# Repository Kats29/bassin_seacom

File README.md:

# Bassin Laboratoire SEACom - ISEN

Ce projet vise à remettre le bassin de test du laboratoire SEACom de l'ISEN au goût du jour. Pour cela, une interface Web est déployée sur un serveur Ethernet hébergé sur une carte Beaglebone Black qui communique avec le bassin via un shield customisé.

## TODO

### Partie Logicielle

- écrire une suite de tests exhaustive qui permet de comprendre ce qui doit être envoyé par le backend en fonction des commandes exécutées
- définir les trames de messages dans la documentation
- compléter la description de cette documentation (à partir de "Redémarrage des commandes numériques (RESET)")

### Partie Matérielle

- Imprimer ou découper à la CNC le couvercle du boitier de la carte
- Ajouter la vitre plexi devant les LED
- Produire la nouvelle version de la carte électronique
- acheter les différents composant manquant pour autonomiser le boitier
	- [prise filtre 230V](https://fr.rs-online.com/web/p/filtres-iec/1676800?searchId=2fb21e5c-5856-4a20-a56e-df45db2b0a76) (ça sera serré mais normalement ça passe)
    - [Alim 5V](https://fr.rs-online.com/web/p/alimentations-a-decoupage/0413673?searchId=7ffa1f5d-4cfa-4edf-9e52-69dc6d7725a8)
    - connecteur DB9 de facade

## Installation

### Configuration de la carte Beaglebone

Premièrement, afin d'avoir accès à tous les ports GPIO de la carte, celle-ci doit être démarrée à partir d'une carte SD au lieu de sa mémoire interne. Pour ce faire, téléchargez [la dernière image de Debian pour Beaglenone Black](https://www.beagleboard.org/distros) et flashez-la sur votre carte SD. Faites attention de bien choisir une image et non pas un flasher eMMC (le nom devrait finir par `4GB microSD IoT`).

Puisque les dernières versions ont un serveur nginx préinstallé, c'est ce que ce projet va utiliser.

Afin de vous connecter au Beaglebone, connecter le câble ethernet à votre pc et configurer votre carte réseau pour avoir une IPv4 telle que 192.168.7.4, via la commande `sudo ifconfig enp3s0 192.168.7.4` (en remplaçant enp3s0 par le nom de votre interface réseau).

Une fois la carte SD insérée dans la Beaglebone et celle-ci branchée sur le même réseau que votre ordinateur, vous pourrez ouvrir une console `ssh` grâce à la commande suivante :

```sh
ssh debian@192.168.7.3
```

Le mot de passe par défaut est `temppwd`.

Afin de configurer nginx, ouvrez le fichier `/etc/nginx/sites-enabled/default` et remplacez la ligne `root /var/www` par `root /home/debian/dist`. Enregistrez le fichier.

Finalement, il faut ouvrir le port 3333 de la Beaglebone pour permettre la connection TCP entre l'interface et le backend :

```sh
sudo nft add table ip filter
sudo nft add chain ip filter INPUT { type filter hook input priority 0 \; }
sudo nft add rule ip filter INPUT tcp dport 3333 accept
sudo nft list ruleset # pour vérifier que les règles ont bien été appliquées
sudo nft list ruleset | sudo tee -a /etc/nftables.conf # pour les sauvegarder
```

Vous pouvez maintenant quitter la console `ssh` avec la commande :

```sh
exit
```

### Compilation du projet

La compilation nécessite d'avoir podman, podman-compose et git d'installés sur le pc.
Clonez et compilez le projet GitHub sur votre ordinateur avec les commandes suivantes :

```sh
git clone https://github.com/Kats29/bassin_seacom.git
cd bassin_seacom
podman build .
podman compose run --rm arm-builder
```

Une fois que le projet est bien compilé (penser à vérifier les logs pour cela) vous pouvez envoyer la release sur la Beaglebone via le script `./.send.sh`.

Tapez le mot de passe de la Beaglebone lorsqu'il vous est demandé.

Vous pouvez à présent rouvrir une console `ssh` pour démarrer le backend :

```sh
ssh debian@192.168.7.3
```

Tapez le mot de passe.

```sh
sudo systemctl restart backend.service
```

Si tout va bien, vous devez avoir quelque chose qui ressemble à ci-dessous en tapant la commande  `sudo systemctl status backend.service` :
```sh
● backend.service - Backend du bassin
     Loaded: loaded (/etc/systemd/system/backend.service; enabled; preset: enabled)
     Active: active (running) since Fri 2025-03-14 21:15:03 CET; 5s ago
   Main PID: 2041 (backend)
      Tasks: 1 (limit: 1024)
     Memory: 72.0K
        CPU: 61ms
     CGroup: /system.slice/backend.service
             └─2041 /home/debian/backend

Mar 14 21:15:03 bassin systemd[1]: Started backend.service - Backend du bassin.
Mar 14 21:15:03 bassin backend[2041]: Starting backend...
```

Si vous souhaitez éditer la configuration du service, elle se trouve ici `/etc/systemd/system/backend.service` et nécessite un redémarrage de systemctl via `sudo systemctl daemon-reload`.

### Accès à l'interface

Vous pouvez à présent vous connecter à l'interface depuis votre navigateur internet, en tapant `192.168.7.3:9090` dans la barre d'adresse.

## Branchement

### Installation de la Beaglebone

### Raccordement réseau

### Communication avec le bassin

## Documentation

Une fois le projet cloné, la documentation technique du code peut être générée grâce à la commande :

```sh
make doc
```

La documentation devrait s'ouvrir dans un navigateur. Sinon, elle peut être visualisée dans un navigateur en ouvrant les fichiers `index.html` générés dans `target/doc/common`, `target/armv7-unknown-linux-musleabihf/doc/backend` et `target/wasm32-unknown-unknown/doc/frontend`

## Utilisation

L'accès se fait via deux plateformes : [cockpit](https://192.168.7.3:9090/system) pour le monitoring et le [site web pour le contrôle des bras](http://192.168.7.3/).

### Apparence et organisation

L'interface est constituée d'une seule vue, qui est séparée en trois zones : une vue centrale, et deux panneaux latéraux. En cas de nécéssité, une fenêtre d'erreur peut également s'ouvrir devant la vue centrale.

#### Vue centrale

La vue centrale représente une visualisation de l'état actuel du bassin, ainsi que des commandes prévues.

Sa partie supérieure montre une vue du dessus en séparant les moitiés droite et gauche du bassin. La même séparation est visible sur la partie inférieure, qui elle montre une vue de côté du bassin (pour visualiser la profondeur).

Les cadres noirs délimitent les zones où chacun des deux bras peut se déplacer, et les symboles  en noir symbolisent la position actuelle de chaque bras. Les symboles  grisés montrent le prochain mouvement pouvant être ajouté.

#### Panneau gauche

Le panneau latéral gauche montre deux choses :

* Les coordonnées du prochain mouvement à ajouter pour chaque bras.

* L'état actuel du bassin, sous formes d'indicateurs colorés (rouges ou verts, gris si le bassin n'est pas connecté).
	* En face de chaque coordonnée, un indicateur passe au rouge si un mouvement est en cours sur cet axe.
	* Sous les coordonnées, d'autres informations sont données sous cette forme.

#### Panneau droit

Le panneau latéral droit montre simplement la liste des mouvement prévus pour chaque bras, dans l'ordre chronologique.

#### Fenêtre d'erreur

### Commandes d'alimentation

La première chose à faire pour allumer le bassin est de le mettre physiquement sous tension. Une fois que c'est fait, l'alimentation peut être contrôlée à distance par l'interface.

#### Allumer le bassin

Pour allumer le bassin, allez dans le menu `Alimentation` et cliquez sur `Démarrer`. Après un démarrage de cette façon, une commande de RESET (expliquée plus loin) et de remise à l'origine doivent obligatoirement être effectuées dans cet ordre.

Après appui, les indicateurs `Bassin alimenté` et `Bassin démarré` devraient être au vert.

#### Éteindre le bassin

Une fois le bassin sous tension et démarré, le menu `Alimentation` devrait contenir un bouton `Arrêter`, qui doit éteindre le bassin.

Après appui, l'indicateur `Bassin démarré` devrait repasser au rouge.

#### Redémarrage des commandes numériques (RESET)

### Gestion des mouvements

#### Ajouter un mouvement

#### Supprimer un mouvement

#### Modifier un mouvement

### Effectuer un mouvement

#### Commandes générales

#### Commandes par bras

#### Commandes par axe

### Sauvegarde et importation de positions

#### Sauvegarder la configuration

#### Importer une configuration

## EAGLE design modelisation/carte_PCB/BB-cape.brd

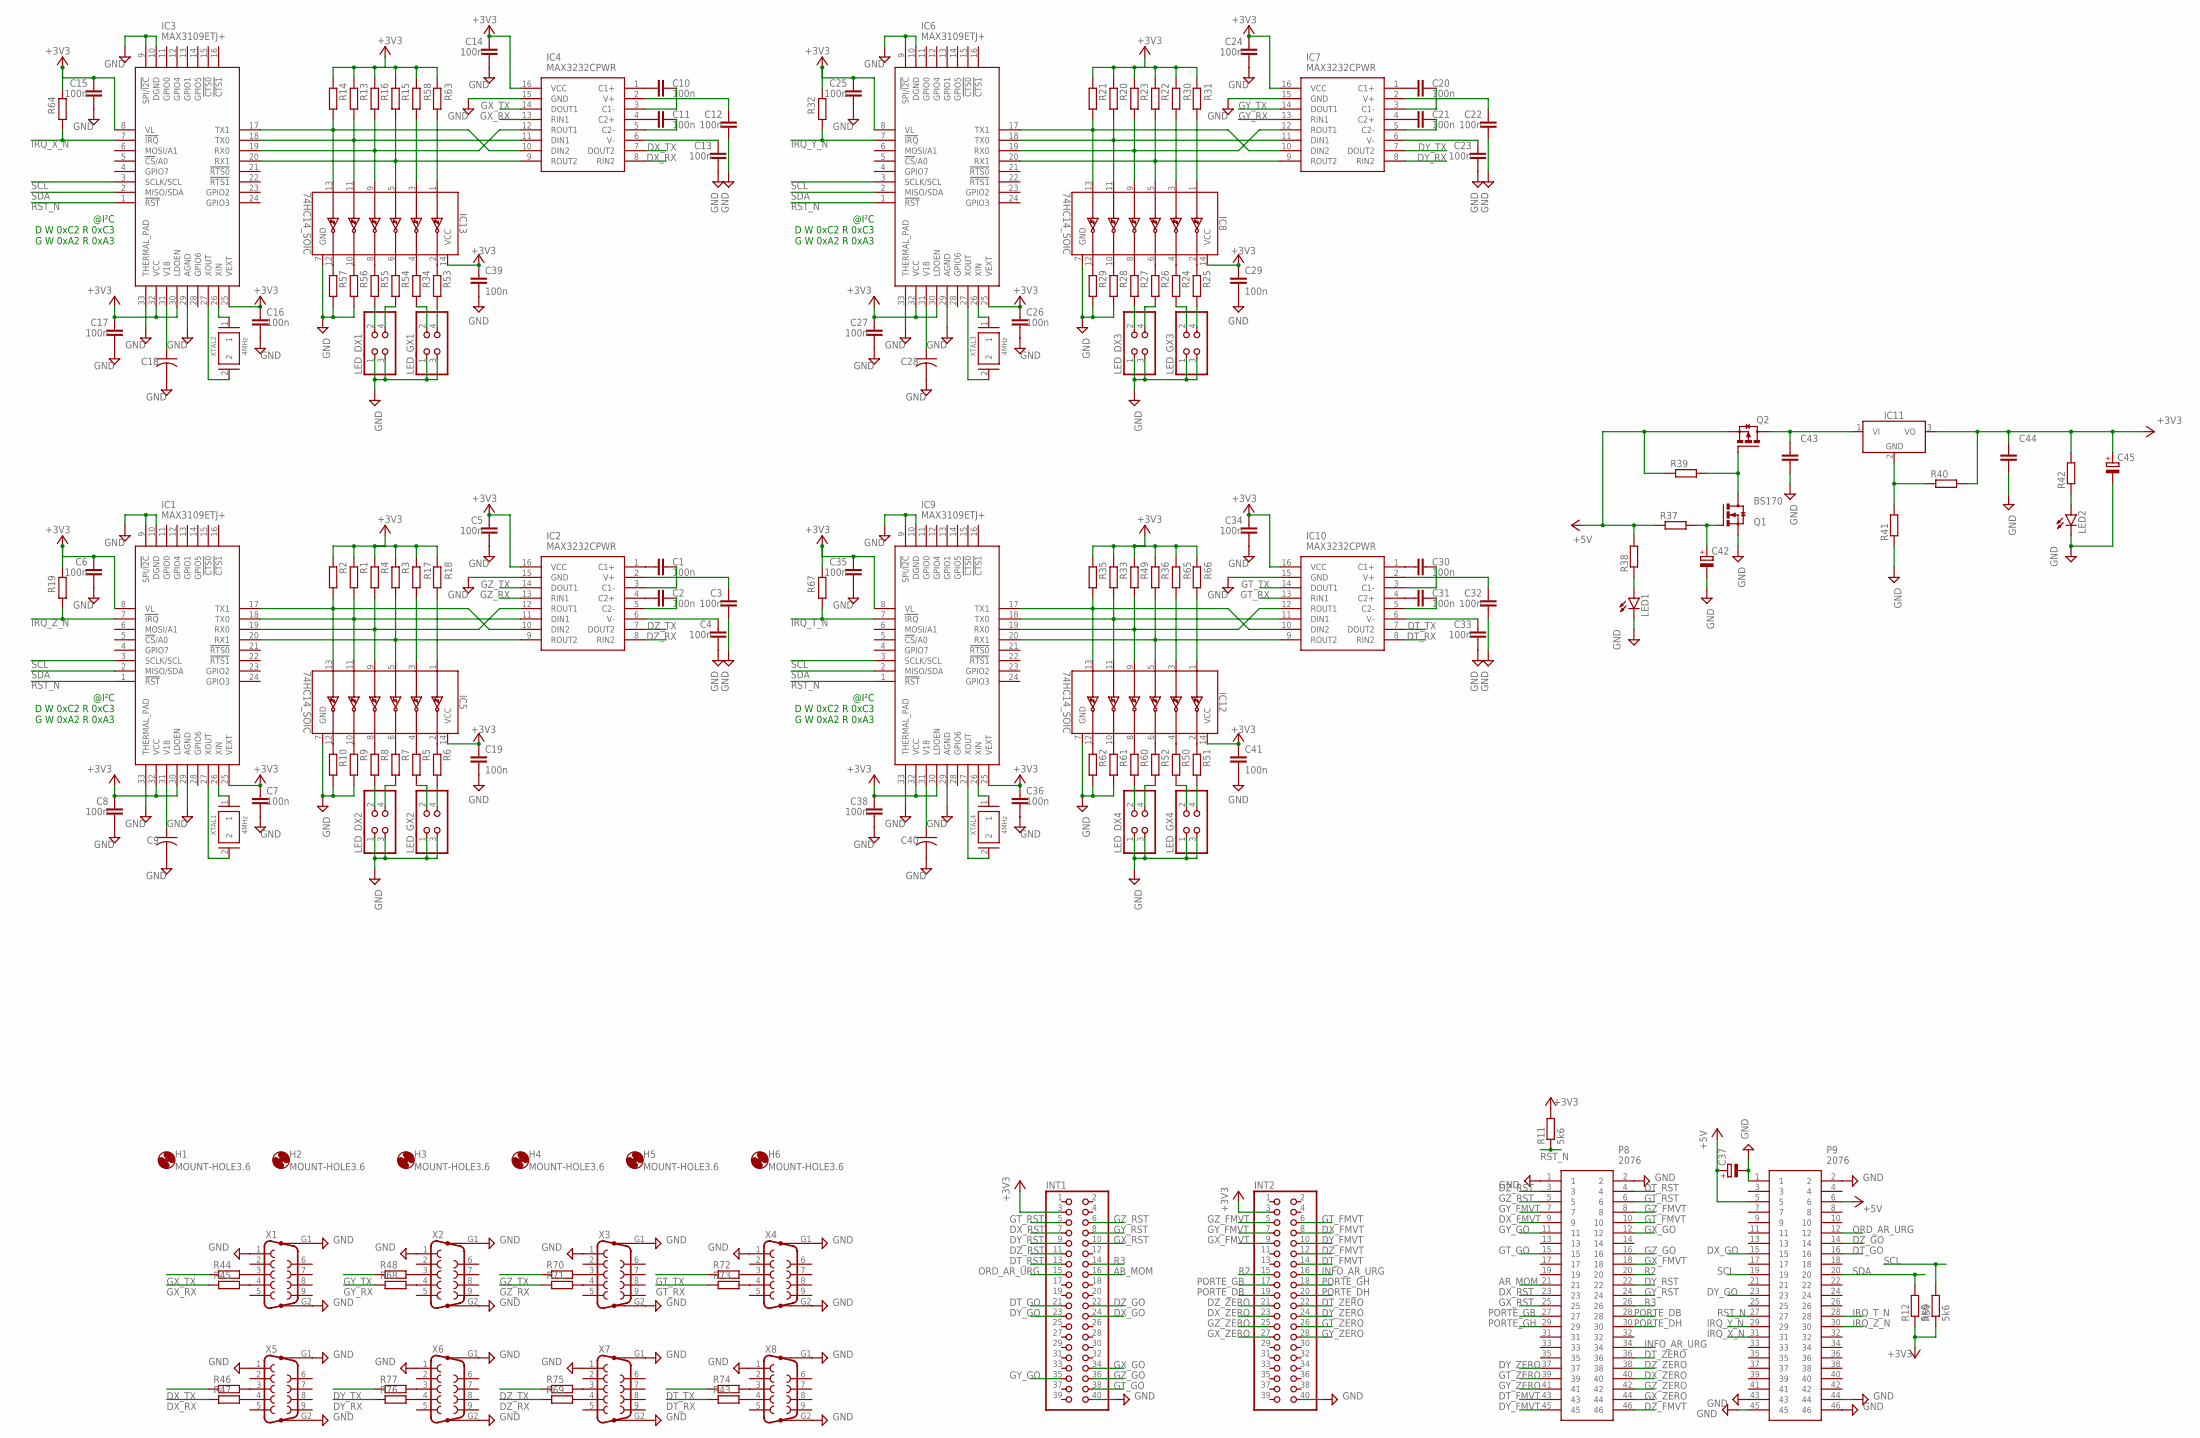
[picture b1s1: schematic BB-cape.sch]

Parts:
C1, C2, C3, C4, C5, C6, C7, C8, C10, C11, C12, C13, C14, C15, C16, C17, C19, C20, C21, C22, C23, C24, C25, C26, C27, C29, C30, C31, C32, C33, C34, C35, C36, C38, C39, C41: 100n; C0603
C9, C18, C28, C40: C-USC1206; C1206
C37, C42, C45: CPOL-EUE2.5-6; E2,5-6
C43, C44: C_CHIP-1210(3225-METRIC); CAPC3225X135
H1, H2, H3, H4, H5, H6: MOUNT-HOLE3.6; 3,6
IC1, IC3, IC6, IC9: MAX3109ETJ+; QFN50P500X500X80-33N
IC2, IC4, IC7, IC10: MAX3232CPWR; SOP65P640X120-16N
IC5, IC8, IC12, IC13: 74HC14_SOIC; SOIC127P600X175-14N
IC11: LM7805_TO220V; TO220V
INT1, INT2: PINHD-2X20; 2X20
LED1, LED2: TLLY4400; LED3MM
LED_DX1, LED_DX2, LED_DX3, LED_DX4: PINHD-2X2; 2X02
LED_GX1, LED_GX2, LED_GX3, LED_GX4: PINHD-2X2; 2X02
P8, P9: 2076; HDRV46W64P254_2X23_5842X500X87
Q1: BS170; TO92-3
Q2: IRF9540PBF; TO-220
R1, R2, R3, R4, R5, R6, R7, R8, R9, R10, R13, R14, R15, R16, R17, R18, R19, R20, R21, R22, R23, R24, R25, R26, R27, R28, R29, R30, R31, R32, R33, R34, R35, R36, R37, R38, R39, R40, R41, R42, R43, R44, R45, R46, R47, R48, R49, R50, R51, R52, R53, R54, R55, R56, R57, R58, R60, R61, R62, R63, R64, R65, R66, R67, R68, R69, R70, R71, R72, R73, R74, R75, R76, R77: R-EU_R0603; R0603
R11, R12, R59: 5k6; R0603
X1, X2, X3, X4, X5, X6, X7, X8: F09HP
XTAL1, XTAL2, XTAL3, XTAL4: 4MHz; XTAL1147X477X420N

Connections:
+3V3: C5.1, C6.1, C7.2, C8.2, C14.1, C15.1, C16.2, C17.2, C19.2, C24.1, C25.1, C26.2, C27.2, C29.2, C34.1, C35.1, C36.2, C38.2, C39.2, C41.2, C44.1, C45.+, IC1.8 (VL), IC1.25 (VEXT), IC1.30 (LDOEN), IC1.32 (VCC), IC2.16 (VCC), IC3.8 (VL), IC3.25 (VEXT), IC3.30 (LDOEN), IC3.32 (VCC), IC4.16 (VCC), IC5.14 (VCC), IC6.8 (VL), IC6.25 (VEXT), IC6.30 (LDOEN), IC6.32 (VCC), IC7.16 (VCC), IC8.14 (VCC), IC9.8 (VL), IC9.25 (VEXT), IC9.30 (LDOEN), IC9.32 (VCC), IC10.16 (VCC), IC11.3 (VO), IC12.14 (VCC), IC13.14 (VCC), INT1.3, INT2.3, R1.1, R2.1, R3.2, R4.2, R11.2, R12.1, R13.1, R14.1, R15.2, R16.2, R17.1, R18.1, R19.2, R20.1, R21.1, R22.2, R23.2, R30.1, R31.1, R32.2, R33.1, R35.1, R36.2, R40.2, R42.2, R49.2, R58.1, R59.1, R63.1, R64.2, R65.1, R66.1, R67.2
+5V: C37.+, P9.5, P9.6, Q2.S, R37.1, R38.2, R39.1
AR_MOM: INT1.16, P8.21
DT_FMVT: INT2.14, P8.43
DT_GO: INT1.21, P9.16
DT_RST: INT1.13, P8.4
DT_RX: IC10.8 (RIN2), R43.1
DT_TX: IC10.7 (DOUT2), R74.1
DT_ZERO: INT2.22, P8.36
DX_FMVT: INT2.8, P8.9
DX_GO: INT1.24, P9.15
DX_RST: INT1.7, P8.23
DX_RX: IC4.8 (RIN2), R47.1
DX_TX: IC4.7 (DOUT2), R46.1
DX_ZERO: INT2.23, P8.40
DY_FMVT: INT2.10, P8.45
DY_GO: INT1.23, P9.23
DY_RST: INT1.9, P8.22
DY_RX: IC7.8 (RIN2), R76.1
DY_TX: IC7.7 (DOUT2), R77.1
DY_ZERO: INT2.24, P8.37
DZ_FMVT: INT2.12, P8.46
DZ_GO: INT1.22, P9.14
DZ_RST: INT1.11, P8.3
DZ_RX: IC2.8 (RIN2), R69.1
DZ_TX: IC2.7 (DOUT2), R75.1
DZ_ZERO: INT2.21, P8.38
GND: C3.1, C4.2, C5.2, C6.2, C7.1, C8.1, C9.2, C12.1, C13.2, C14.2, C15.2, C16.1, C17.1, C18.2, C19.1, C22.1, C23.2, C24.2, C25.2, C26.1, C27.1, C28.2, C29.1, C32.1, C33.2, C34.2, C35.2, C36.1, C37.-, C38.1, C39.1, C40.2, C41.1, C42.-, C43.2, C44.2, C45.-, IC1.9 (SPI/!I2C), IC1.10 (DGND), IC1.29 (AGND), IC1.33 (THERMAL_PAD), IC2.15 (GND), IC3.9 (SPI/!I2C), IC3.10 (DGND), IC3.29 (AGND), IC3.33 (THERMAL_PAD), IC4.15 (GND), IC5.7 (GND), IC6.9 (SPI/!I2C), IC6.10 (DGND), IC6.29 (AGND), IC6.33 (THERMAL_PAD), IC7.15 (GND), IC8.7 (GND), IC9.9 (SPI/!I2C), IC9.10 (DGND), IC9.29 (AGND), IC9.33 (THERMAL_PAD), IC10.15 (GND), IC12.7 (GND), IC13.7 (GND), INT1.40, INT2.40, LED1.K (C), LED2.K (C), LED_DX1.1, LED_DX1.3, LED_DX2.1, LED_DX2.3, LED_DX3.1, LED_DX3.3, LED_DX4.1, LED_DX4.3, LED_GX1.1, LED_GX1.3, LED_GX2.1, LED_GX2.3, LED_GX3.1, LED_GX3.3, LED_GX4.1, LED_GX4.3, P8.1, P8.2, P9.1, P9.2, P9.43, P9.44, P9.45, P9.46, Q1.3 (S), R9.2, R10.2, R28.2, R29.2, R41.1, R56.2, R57.2, R61.2, R62.2, X1.1, X1.G1, X1.G2, X2.1, X2.G1, X2.G2, X3.1, X3.G1, X3.G2, X4.1, X4.G1, X4.G2, X5.1, X5.G1, X5.G2, X6.1, X6.G1, X6.G2, X7.1, X7.G1, X7.G2, X8.1, X8.G1, X8.G2
GT_FMVT: INT2.6, P8.10
GT_GO: INT1.38, P8.15
GT_RST: INT1.5, P8.6
GT_RX: IC10.13 (RIN1), R73.1
GT_TX: IC10.14 (DOUT1), R72.1
GT_ZERO: INT2.26, P8.39
GX_FMVT: INT2.9, P8.18
GX_GO: INT1.34, P8.12
GX_RST: INT1.10, P8.25
GX_RX: IC4.13 (RIN1), R45.1
GX_TX: IC4.14 (DOUT1), R44.1
GX_ZERO: INT2.27, P8.44
GY_FMVT: INT2.7, P8.7
GY_GO: INT1.35, P8.11
GY_RST: INT1.8, P8.24
GY_RX: IC7.13 (RIN1), R68.1
GY_TX: IC7.14 (DOUT1), R48.1
GY_ZERO: INT2.28, P8.41
GZ_FMVT: INT2.5, P8.8
GZ_GO: INT1.36, P8.16
GZ_RST: INT1.6, P8.5
GZ_RX: IC2.13 (RIN1), R71.1
GZ_TX: IC2.14 (DOUT1), R70.1
GZ_ZERO: INT2.25, P8.42
INFO_AR_URG: INT2.16, P8.34
IRQ_T_N: IC9.7 (!IRQ), P9.28, R67.1
IRQ_X_N: IC3.7 (!IRQ), P9.31, R64.1
IRQ_Y_N: IC6.7 (!IRQ), P9.29, R32.1
IRQ_Z_N: IC1.7 (!IRQ), P9.30, R19.1
unnamed: C3.2, IC2.2 (V+)
unnamed: C1.1, IC2.3 (C1-)
unnamed: C2.1, IC2.5 (C2-)
unnamed: C4.1, IC2.6 (V-)
unnamed: IC1.26 (XIN), XTAL1.1
unnamed: IC1.27 (XOUT), XTAL1.2
unnamed: C42.+, Q1.2 (G), R37.2
unnamed: LED_DX2.2, R8.2
unnamed: LED_DX2.4, R7.2
unnamed: LED_GX2.2, R5.2
unnamed: LED1.A, R38.1
unnamed: C12.2, IC4.2 (V+)
unnamed: Q1.1 (D), Q2.G, R39.2
unnamed: LED_GX2.4, R6.2
unnamed: C9.1, IC1.31 (V18)
unnamed: C10.1, IC4.3 (C1-)
unnamed: C11.1, IC4.5 (C2-)
unnamed: C13.1, IC4.6 (V-)
unnamed: IC3.26 (XIN), XTAL2.1
unnamed: IC3.27 (XOUT), XTAL2.2
unnamed: C43.1, IC11.1 (VI), Q2.D
unnamed: IC11.2 (GND), R40.1, R41.2
unnamed: IC1.17 (TX1), IC2.10 (DIN2), IC5.13 (6A), R2.2
unnamed: IC1.18 (TX0), IC2.11 (DIN1), IC5.11 (5A), R1.2
unnamed: IC1.19 (RX0), IC2.12 (ROUT1), IC5.9 (4A), R4.1
unnamed: LED_DX1.2, R55.2
unnamed: IC1.20 (RX1), IC2.9 (ROUT2), IC5.5 (3A), R3.1
unnamed: IC5.3 (2A), R17.2
unnamed: IC5.1 (1A), R18.2
unnamed: C1.2, IC2.1 (C1+)
unnamed: R44.2, X1.3
unnamed: LED2.A, R42.1
unnamed: R45.2, X1.4
unnamed: C2.2, IC2.4 (C2+)
unnamed: IC5.4 (2Y), R5.1
unnamed: IC5.2 (1Y), R6.1
unnamed: IC5.6 (3Y), R7.1
unnamed: IC5.8 (4Y), R8.1
unnamed: IC5.10 (5Y), R9.1
unnamed: IC5.12 (6Y), R10.1
unnamed: C22.2, IC7.2 (V+)
unnamed: C20.1, IC7.3 (C1-)
unnamed: C21.1, IC7.5 (C2-)
unnamed: C23.1, IC7.6 (V-)
unnamed: IC6.26 (XIN), XTAL3.1
unnamed: IC6.27 (XOUT), XTAL3.2
unnamed: LED_DX3.2, R27.2
unnamed: LED_DX3.4, R26.2
unnamed: LED_GX3.2, R24.2
unnamed: LED_GX3.4, R25.2
unnamed: C28.1, IC6.31 (V18)
unnamed: IC6.17 (TX1), IC7.10 (DIN2), IC8.13 (6A), R21.2
unnamed: IC6.18 (TX0), IC7.11 (DIN1), IC8.11 (5A), R20.2
unnamed: IC6.19 (RX0), IC7.12 (ROUT1), IC8.9 (4A), R23.1
unnamed: IC6.20 (RX1), IC7.9 (ROUT2), IC8.5 (3A), R22.1
unnamed: IC8.3 (2A), R30.2
unnamed: IC8.1 (1A), R31.2
unnamed: C20.2, IC7.1 (C1+)
unnamed: C21.2, IC7.4 (C2+)
unnamed: IC8.4 (2Y), R24.1
unnamed: IC8.2 (1Y), R25.1
unnamed: IC8.6 (3Y), R26.1
unnamed: IC8.8 (4Y), R27.1
unnamed: IC8.10 (5Y), R28.1
unnamed: IC8.12 (6Y), R29.1
unnamed: C32.2, IC10.2 (V+)
unnamed: C30.1, IC10.3 (C1-)
unnamed: C31.1, IC10.5 (C2-)
unnamed: C33.1, IC10.6 (V-)
unnamed: LED_DX1.4, R54.2
unnamed: LED_GX1.2, R34.2
unnamed: IC9.26 (XIN), XTAL4.1
unnamed: LED_GX1.4, R53.2
unnamed: C18.1, IC3.31 (V18)
unnamed: IC9.27 (XOUT), XTAL4.2
unnamed: LED_DX4.2, R60.2
unnamed: IC3.17 (TX1), IC4.10 (DIN2), IC13.13 (6A), R14.2
unnamed: R46.2, X5.3
unnamed: IC3.18 (TX0), IC4.11 (DIN1), IC13.11 (5A), R13.2
unnamed: LED_DX4.4, R52.2
unnamed: IC3.19 (RX0), IC4.12 (ROUT1), IC13.9 (4A), R16.1
unnamed: LED_GX4.2, R50.2
unnamed: LED_GX4.4, R51.2
unnamed: IC3.20 (RX1), IC4.9 (ROUT2), IC13.5 (3A), R15.1
unnamed: C40.1, IC9.31 (V18)
unnamed: IC9.17 (TX1), IC10.10 (DIN2), IC12.13 (6A), R35.2
unnamed: IC13.3 (2A), R58.2
unnamed: IC9.18 (TX0), IC10.11 (DIN1), IC12.11 (5A), R33.2
unnamed: IC9.19 (RX0), IC10.12 (ROUT1), IC12.9 (4A), R49.1
unnamed: IC13.1 (1A), R63.2
unnamed: IC9.20 (RX1), IC10.9 (ROUT2), IC12.5 (3A), R36.1
unnamed: IC12.3 (2A), R65.2
unnamed: R47.2, X5.4
unnamed: R48.2, X2.3
unnamed: R68.2, X2.4
unnamed: R70.2, X3.3
unnamed: R71.2, X3.4
unnamed: R69.2, X7.4
unnamed: R72.2, X4.3
unnamed: R73.2, X4.4
unnamed: IC12.1 (1A), R66.2
unnamed: C30.2, IC10.1 (C1+)
unnamed: C31.2, IC10.4 (C2+)
unnamed: IC12.4 (2Y), R50.1
unnamed: IC12.2 (1Y), R51.1
unnamed: IC12.6 (3Y), R52.1
unnamed: C10.2, IC4.1 (C1+)
unnamed: C11.2, IC4.4 (C2+)
unnamed: R74.2, X8.3
unnamed: R43.2, X8.4
unnamed: IC13.4 (2Y), R34.1
unnamed: IC13.2 (1Y), R53.1
unnamed: IC12.8 (4Y), R60.1
unnamed: IC12.10 (5Y), R61.1
unnamed: IC13.6 (3Y), R54.1
unnamed: IC13.8 (4Y), R55.1
unnamed: IC12.12 (6Y), R62.1
unnamed: R75.2, X7.3
unnamed: R76.2, X6.4
unnamed: R77.2, X6.3
unnamed: IC13.10 (5Y), R56.1
unnamed: IC13.12 (6Y), R57.1
ORD_AR_URG: INT1.15, P9.12
PORTE_DB: INT2.19, P8.28
PORTE_DH: INT2.20, P8.30
PORTE_GB: INT2.17, P8.27
PORTE_GH: INT2.18, P8.29
R2: INT2.15, P8.20
R3: INT1.14, P8.26
RST_N: IC1.1 (!RST), IC3.1 (!RST), IC6.1 (!RST), IC9.1 (!RST), P9.27, R11.1
SCL: IC1.3 (SCLK/SCL), IC3.3 (SCLK/SCL), IC6.3 (SCLK/SCL), IC9.3 (SCLK/SCL), P9.19, R59.2
SDA: IC1.2 (MISO/SDA), IC3.2 (MISO/SDA), IC6.2 (MISO/SDA), IC9.2 (MISO/SDA), P9.20, R12.2

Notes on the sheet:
@I²C D W 0xC2 R 0xC3 G W 0xA2 R 0xA3

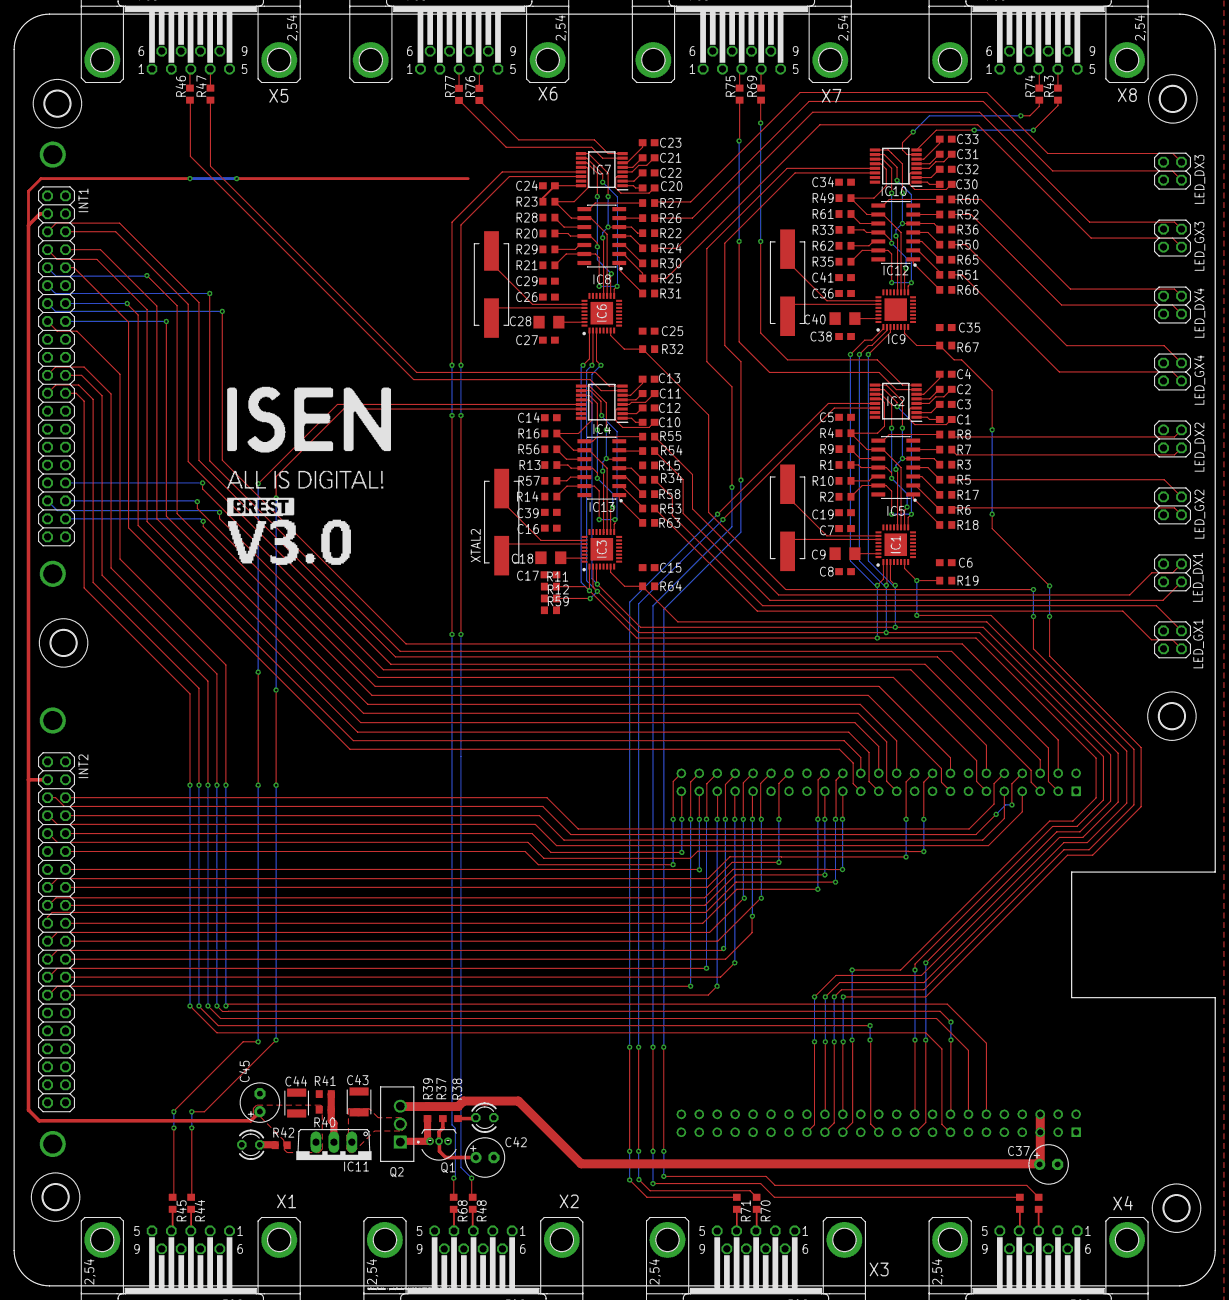
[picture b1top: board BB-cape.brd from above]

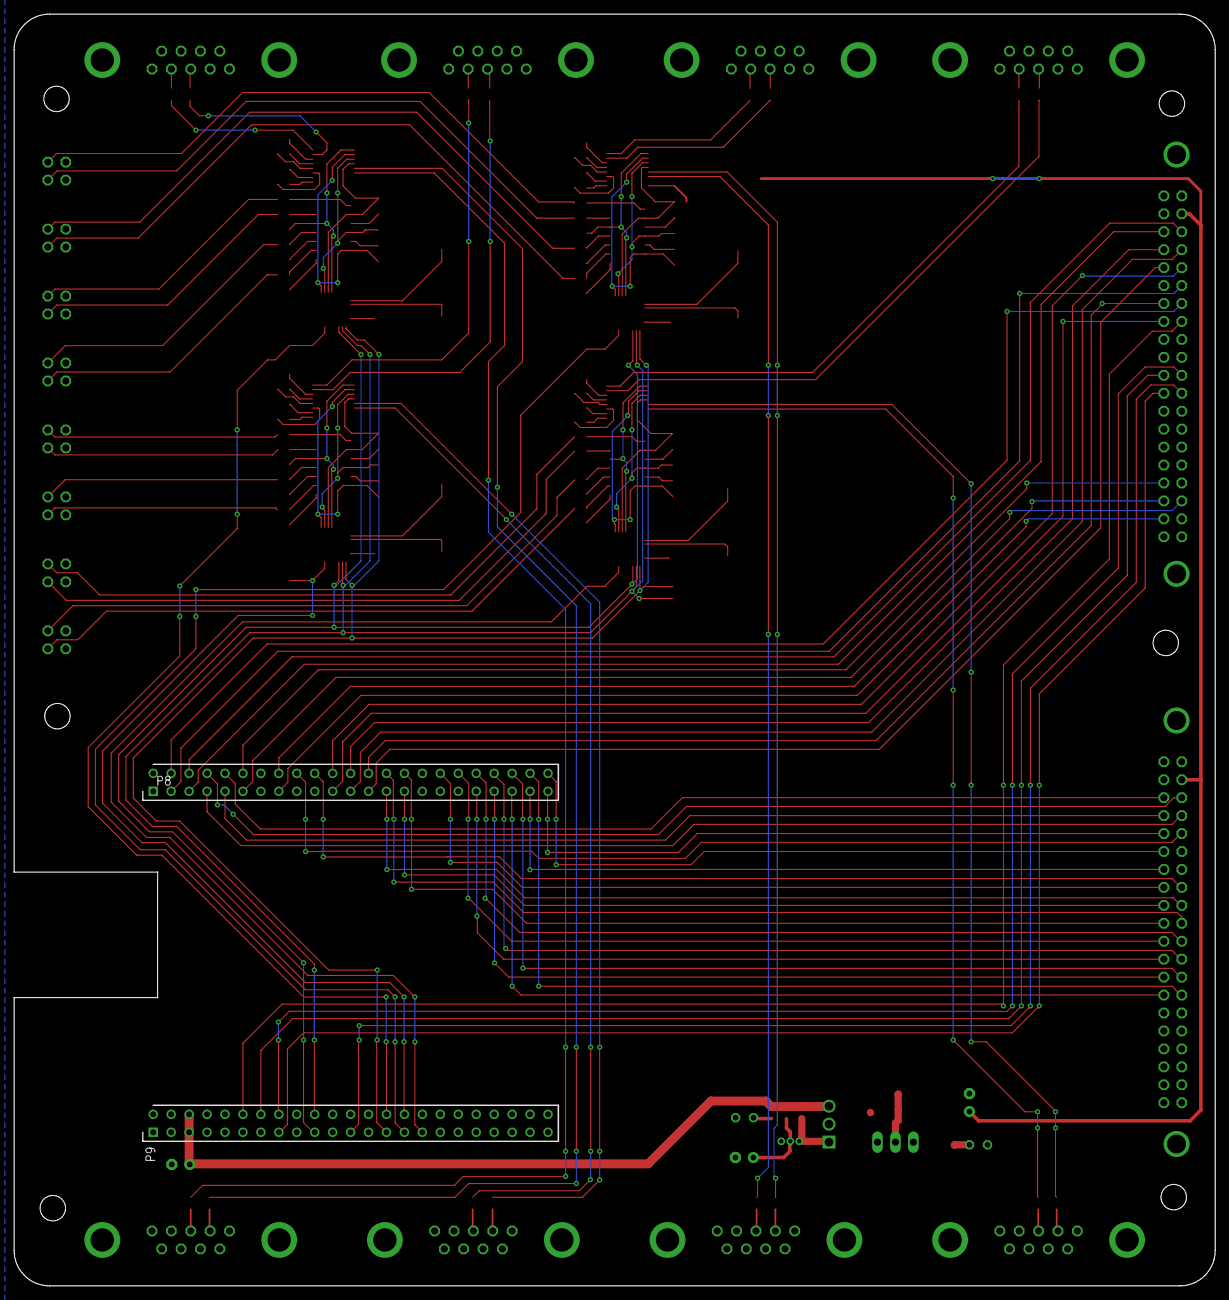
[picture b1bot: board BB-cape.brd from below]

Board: 2 copper layers, 170.0 x 180.0 mm, 169 parts (2 on the bottom side), 189 nets.

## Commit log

2024-01-22 first
2024-01-22 moved libs
2024-01-22 made it work
2024-01-22 added tcp stream client
2024-01-22 Cross-compilation Backend
2024-01-23 Cross-compilation Backend test GPIO
2024-01-23 makefile
2024-01-23 send by makefile
2024-01-23 Implémentation des drivers dans le backend, et ajout des fonctions reset, zereo et ar_mom pour DriverCn
2024-01-24 tcp link works
2024-01-26 tcp_socket
2024-01-26 Création de ArmBackend
2024-01-26 Ajout de la fonction update dans ArmBackend
2024-01-26 added drivers
2024-01-26 it works
2024-01-26 njeik
2024-01-26 Commencement du drivers pour la communication en RS323, via i2c
2024-01-29 FINALLY IT WORKS
2024-01-29 Fin du drivers pour la communication en RS323, via i2c Mise a jour de la classe AmrsBackend pour l'implémenter
2024-01-29 interface
2024-01-29 It works noice
2024-01-29 fjekvmsbnslkgesvd
2024-01-31 Création du système d'erreur
2024-02-02 Update du système d'erreur sur le backend Implémentation du système de commande sur la backend
2024-02-02 Goulven touche au frontend (plus de drifting, frame des différentes vue faite par une fonction, création de problèmes au niveau de l'affichage tu théta)
2024-02-02 Goulven retouche au frontend (et il règle les problèmes au niveau de l'affichage du théta qu'il avait créé)
2024-02-07 Mise ne place du threading tcp pour le backend
2024-02-08 Mise ne place du threading tcp pour le backend partie 2
2024-02-08 frontend stuff
2024-02-09 straightened the UI
2024-02-09 Mise en place d'un système de fichier de log
2024-02-09 Petite maj tu index.html pour enlever des warning
2024-02-09 Création de la structure de status
2024-02-09 mutex madness
2024-03-04 interface improvements
2024-03-05 Amélioration du système de log, et création d'un dossier de log a part
2024-03-06 Ammélioration du polling pour le status : envoie du status que si changement Configuration des drivers I2C vers RS232
2024-03-06 Ajout des fonctions origin_X et move_next_X
2024-03-06 Ajout des commandes pour les cn dans l'interface
2024-03-06 Ajout d'une parti de la list des position suivantes
2024-03-06 Documentation
2024-03-07 Début side panel pour affichage de la liste
2024-03-07 Ajout du chemin sur le panneau de visualisation
2024-03-07 Nouveau format pour la position
2024-03-07 interface formatage
2024-03-07 Ajout de l'attente de fin de mouvement avant chagement affichage
2024-03-07 merge
2024-03-07 pour de vrai cette fois
2024-03-07 changement de couleur des chemins pendant les mouvements
2024-03-08 fin de l'ajout de l'attente de fin de mouvement avant chagement affichage
2024-03-08 Remplacement des sends par les fonctions associées
2024-03-08 Réglage du décalage des vues
2024-03-08 ajout de la gestion de fichiers (marche pas)
2024-03-09 Gestion de fichiers qui fonctionne
2024-03-26 smol mistake
2024-03-26 added base readme
2024-03-26 Réglage partielle suppression dans vec de move
2024-03-26 tests frontend
2024-03-26 Changement du format JSON des fichiers enregistrés et mise en place d'une erreur si format invalide
2024-03-26 Ajout de commentaire pour la doc
2024-03-27 J'ai tout règlé les problèmes
2024-03-28 revert
2024-03-29 i2c disable transmit during write
2024-03-29 Le backend qui marche avec la comm RS232
2024-03-29 frontend mouvements unitaires
2024-03-29 frontend test mouvements
2024-03-29 Frontend qui est sympa
2024-03-29 Bouton arr mom
2026-02-12 docs: fixed some errors and documented how to connect to the beaglebone
2026-02-26 feat: migrated backend deps from websocket to tungstenite and i2c-linux to i2cdev because old crates were not maintained anymore + some linting
2026-02-26 clean: applied some linting to common also
2026-02-26 feat: moved from main to lib in frontend because it is expected from Trunk, also added necessary config to the .toml file, and bumped the getrandom version which was outdated
2026-02-26 build: fixed the build process to make it more readable and verbose for debugging, also using the release version now instead of the debug one for backend, and using direct IP for transfer with .send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
2026-02-26 build: added dockerfile and docker-compose to allow cross compiling easily
2026-02-27 ADD 3D modeling files. enclosure for the pcb
2026-02-27 doc: added the backup of the backend service configuration file and completed the readme with todo and documentation regarding the building of the docker image for cross compile
2026-02-27 ADD 3D modeling files for PCB and electronic makefile
2026-02-27 Update hardware section with new tasks
    Added tasks for hardware component production and procurement.
2026-02-27 doc: added the links to access to cockpit and the website
